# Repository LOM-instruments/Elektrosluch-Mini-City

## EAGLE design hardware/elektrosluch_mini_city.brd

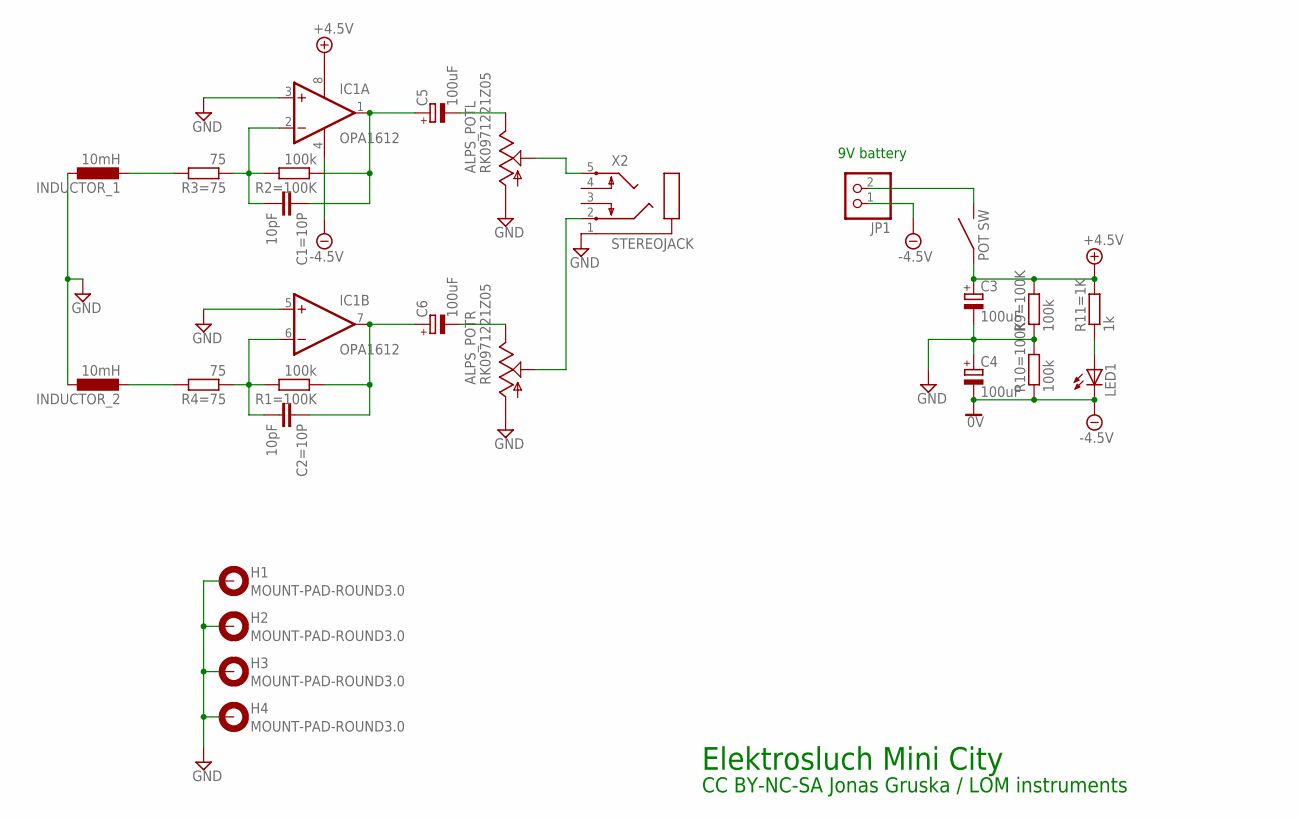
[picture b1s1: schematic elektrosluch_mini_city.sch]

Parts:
ALPS_POT: RK0971221Z05; ALPS_RK0971221Z0X
C1=10P, C2=10P: 10pF; C050-024X044
C3, C4, C5, C6: 100uF; E2,5-6
H1, H2, H3, H4: MOUNT-PAD-ROUND3.0; 3,0-PAD
IC1: OPA1612; SO08
INDUCTOR_1, INDUCTOR_2: 10mH; COIL
JP1: PINHD-1X2; 1X02
LED1: LED3MM
R1=100K, R2=100K, R9=100K, R10=100K: 100k; 0204/7
R3=75, R4=75: 75; 0204/7
R11=1K: 1k; 0204/7
X2: STEREOJACK; STX3100

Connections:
+5V: ALPS_POT.S1, C3.+, IC1.8 (V+), R9=100K.2, R11=1K.2
-5V: C4.-, IC1.4 (V-), JP1.1, LED1.K (C), R10=100K.1
GND: ALPS_POT.G1 (1), ALPS_POT.G2 (1), C3.-, C4.+, H1.B3,0, H2.B3,0, H3.B3,0, H4.B3,0, IC1.3 (+IN), IC1.5 (+IN), INDUCTOR_1.P$1 (1), INDUCTOR_2.P$1 (1), R9=100K.1, R10=100K.2, X2.1
unnamed: C1=10P.2, IC1.2 (-IN), R2=100K.2, R3=75.1
unnamed: C1=10P.1, C5.+, IC1.1 (OUT), R2=100K.1
unnamed: ALPS_POT.I1 (3), C5.-
unnamed: C2=10P.2, IC1.6 (-IN), R1=100K.2, R4=75.1
unnamed: C2=10P.1, C6.+, IC1.7 (OUT), R1=100K.1
unnamed: ALPS_POT.I2 (3), C6.-
unnamed: ALPS_POT.O1 (2), X2.5
unnamed: INDUCTOR_1.P$2 (2), R3=75.2
unnamed: ALPS_POT.O2 (2), X2.2
unnamed: INDUCTOR_2.P$2 (2), R4=75.2
unnamed: LED1.A, R11=1K.1
unnamed: ALPS_POT.S2, JP1.2

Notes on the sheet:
9V battery
Elektrosluch Mini City
CC BY-NC-SA Jonas Gruska / LOM instruments

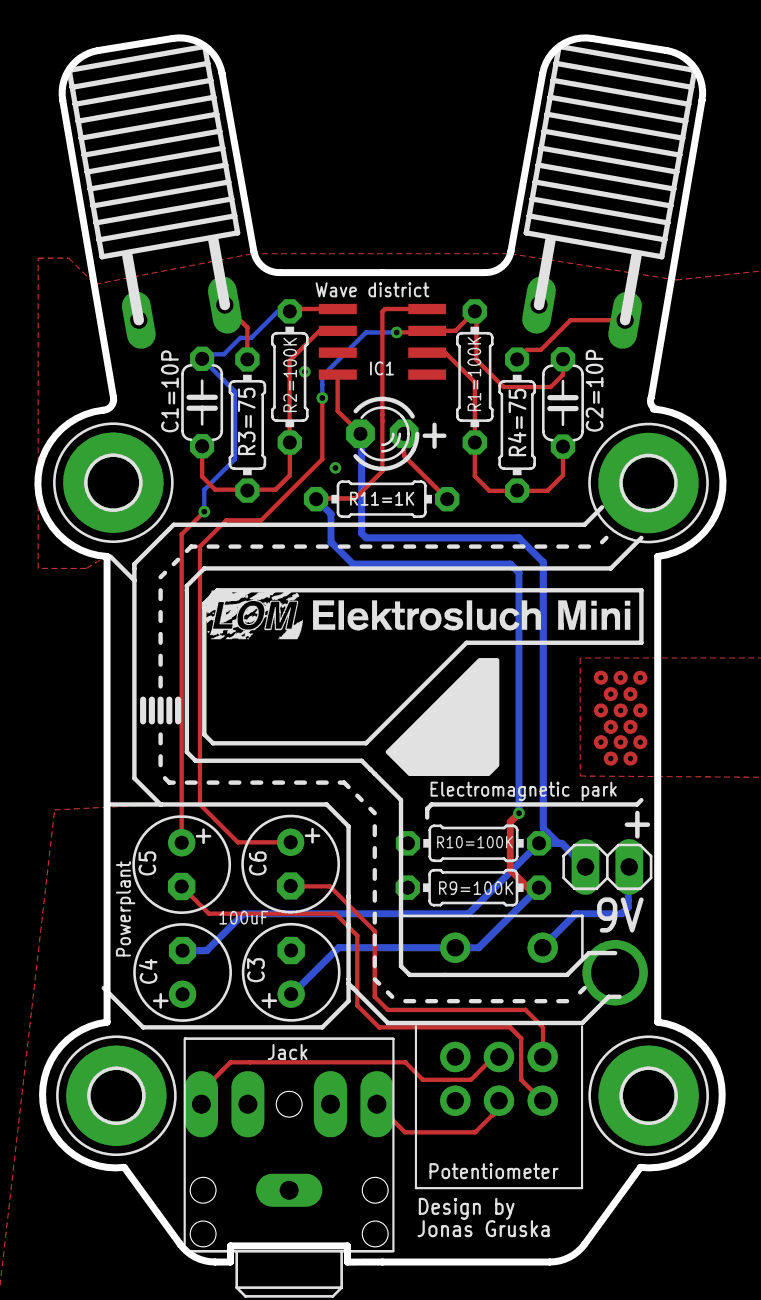
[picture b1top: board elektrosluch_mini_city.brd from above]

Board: 2 copper layers, 39.8 x 71.1 mm, 25 parts (0 on the bottom side), 15 nets.

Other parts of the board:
U$1: ELEKTROSLUCHMINI

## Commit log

2016-11-02 init
2016-11-05 schematic in pdf
2017-10-02 extra step
